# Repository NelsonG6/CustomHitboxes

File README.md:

# My controller
Files for building my controller

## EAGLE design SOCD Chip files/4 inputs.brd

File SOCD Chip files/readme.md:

Sadly, this SOCD chip got banned by Capcom.

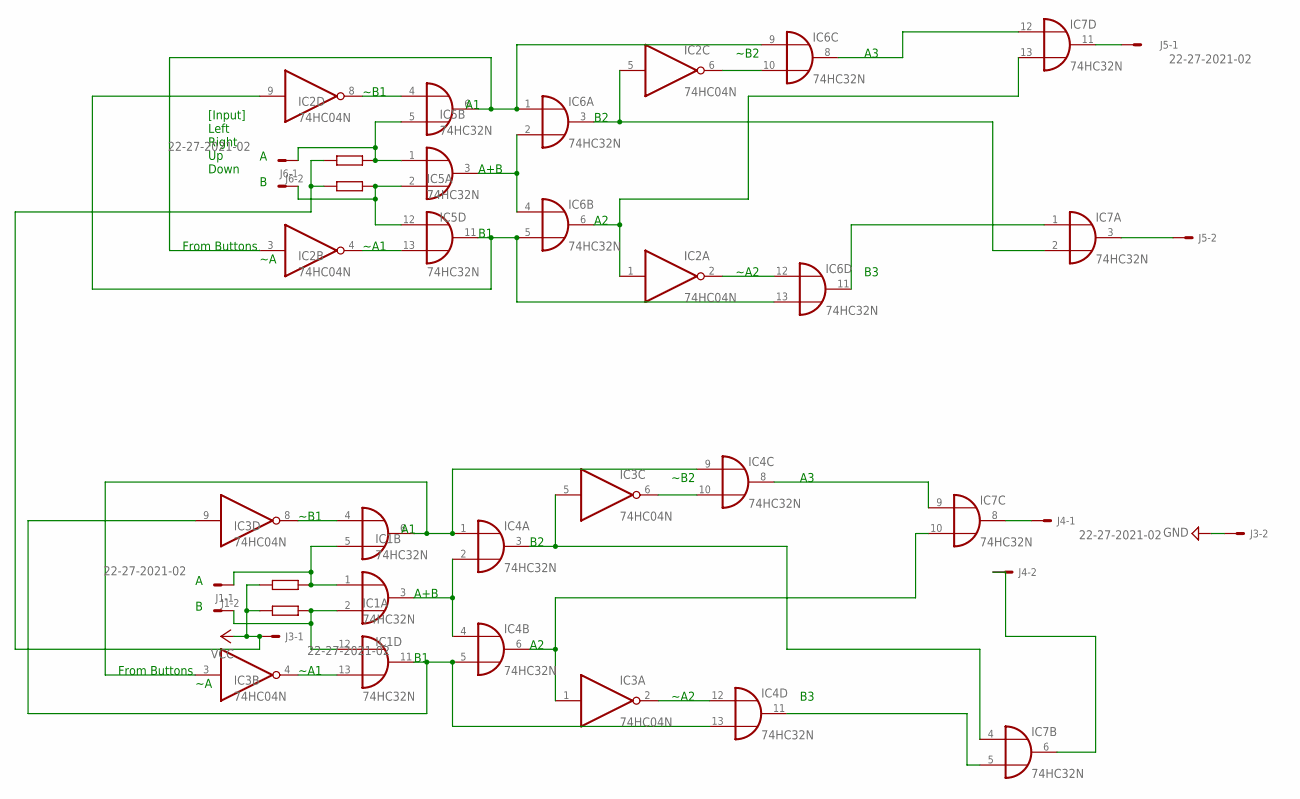
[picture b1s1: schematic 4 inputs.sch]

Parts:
IC1, IC4, IC5, IC6, IC7: 74HC32N; DIL14
IC2, IC3: 74HC04N; DIL14
J1, J3, J4, J5, J6: 22-27-2021-02; 6410-02
R1, R2, R3, R4: R0204/7; 0204/7

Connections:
A0: IC1.1 (I0), IC1.5 (I1), J1.1, R3.2
A1: IC1.6 (O), IC3.3 (I), IC4.1 (I0), IC4.9 (I0)
A2: IC5.1 (I0), IC5.5 (I1), J6.1, R1.2
A2ORA3: IC3.1 (I), IC4.6 (O), IC7.10 (I1)
A2OUT: IC7.11 (O), J5.1
A3: IC2.3 (I), IC5.6 (O), IC6.1 (I0), IC6.9 (I0)
A+B: IC1.3 (O), IC4.2 (I1), IC4.4 (I0)
A+B1: IC5.3 (O), IC6.2 (I1), IC6.4 (I0)
AOUT: IC7.8 (O), J4.1
B0: IC1.2 (I1), IC1.12 (I0), J1.2, R4.2
B1: IC1.11 (O), IC3.9 (I), IC4.5 (I1), IC4.13 (I1)
B2: IC5.2 (I1), IC5.12 (I0), J6.2, R2.2
B2ORB1: IC6.11 (O), IC7.1 (I0)
B2ORB3: IC3.5 (I), IC4.3 (O), IC7.4 (I0)
B2OUT: IC7.3 (O), J5.2
B3: IC2.9 (I), IC5.11 (O), IC6.5 (I1), IC6.13 (I1)
BOUT: IC7.6 (O), J4.2
GND: IC1.7 (GND), IC2.7 (GND), IC3.7 (GND), IC4.7 (GND), IC5.7 (GND), IC6.7 (GND), IC7.7 (GND), J3.2
unnamed: IC6.8 (O), IC7.12 (I0)
unnamed: IC2.5 (I), IC6.3 (O), IC7.2 (I1)
unnamed: IC2.1 (I), IC6.6 (O), IC7.13 (I1)
unnamed: IC4.8 (O), IC7.9 (I0)
unnamed: IC4.11 (O), IC7.5 (I1)
VCC: IC1.14 (VCC), IC2.14 (VCC), IC3.14 (VCC), IC4.14 (VCC), IC5.14 (VCC), IC6.14 (VCC), IC7.14 (VCC), J3.1, R1.1, R2.1, R3.1, R4.1
~A1: IC1.13 (I1), IC3.4 (O)
~A2: IC3.2 (O), IC4.12 (I0)
~A3: IC2.2 (O), IC6.12 (I0)
~A4: IC2.4 (O), IC5.13 (I1)
~B1: IC1.4 (I0), IC3.8 (O)
~B2: IC3.6 (O), IC4.10 (I1)
~B3: IC2.8 (O), IC5.4 (I0)
~B4: IC2.6 (O), IC6.10 (I1)

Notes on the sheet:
A+B
From Buttons
~B1
~A1
~B2
~A2
[Input] Left Right Up Down

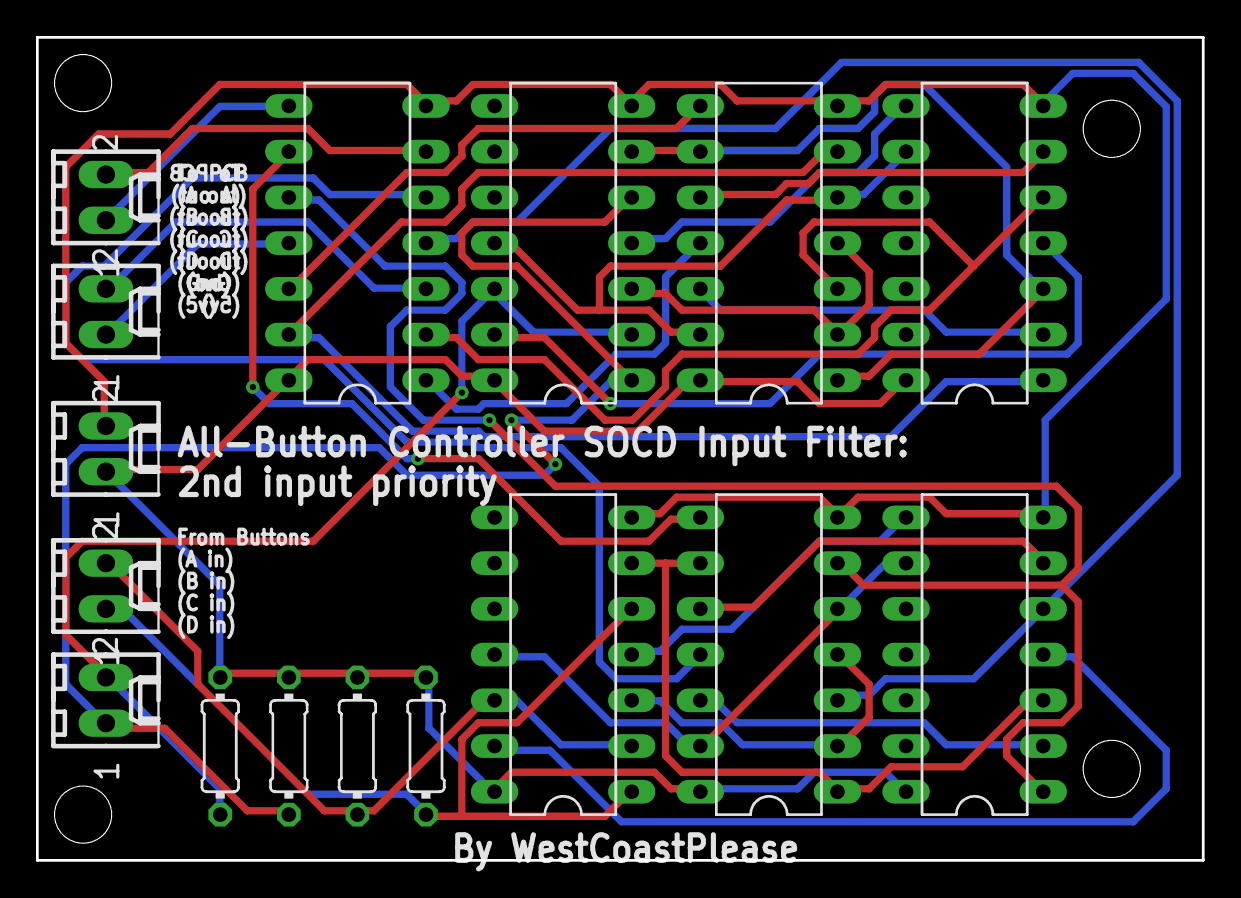
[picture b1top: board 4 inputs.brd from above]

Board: 2 copper layers, 64.8 x 45.7 mm, 16 parts (0 on the bottom side), 32 nets.

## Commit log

2019-06-11 Images
2019-06-11 Image fix
2019-06-20 Renamed
